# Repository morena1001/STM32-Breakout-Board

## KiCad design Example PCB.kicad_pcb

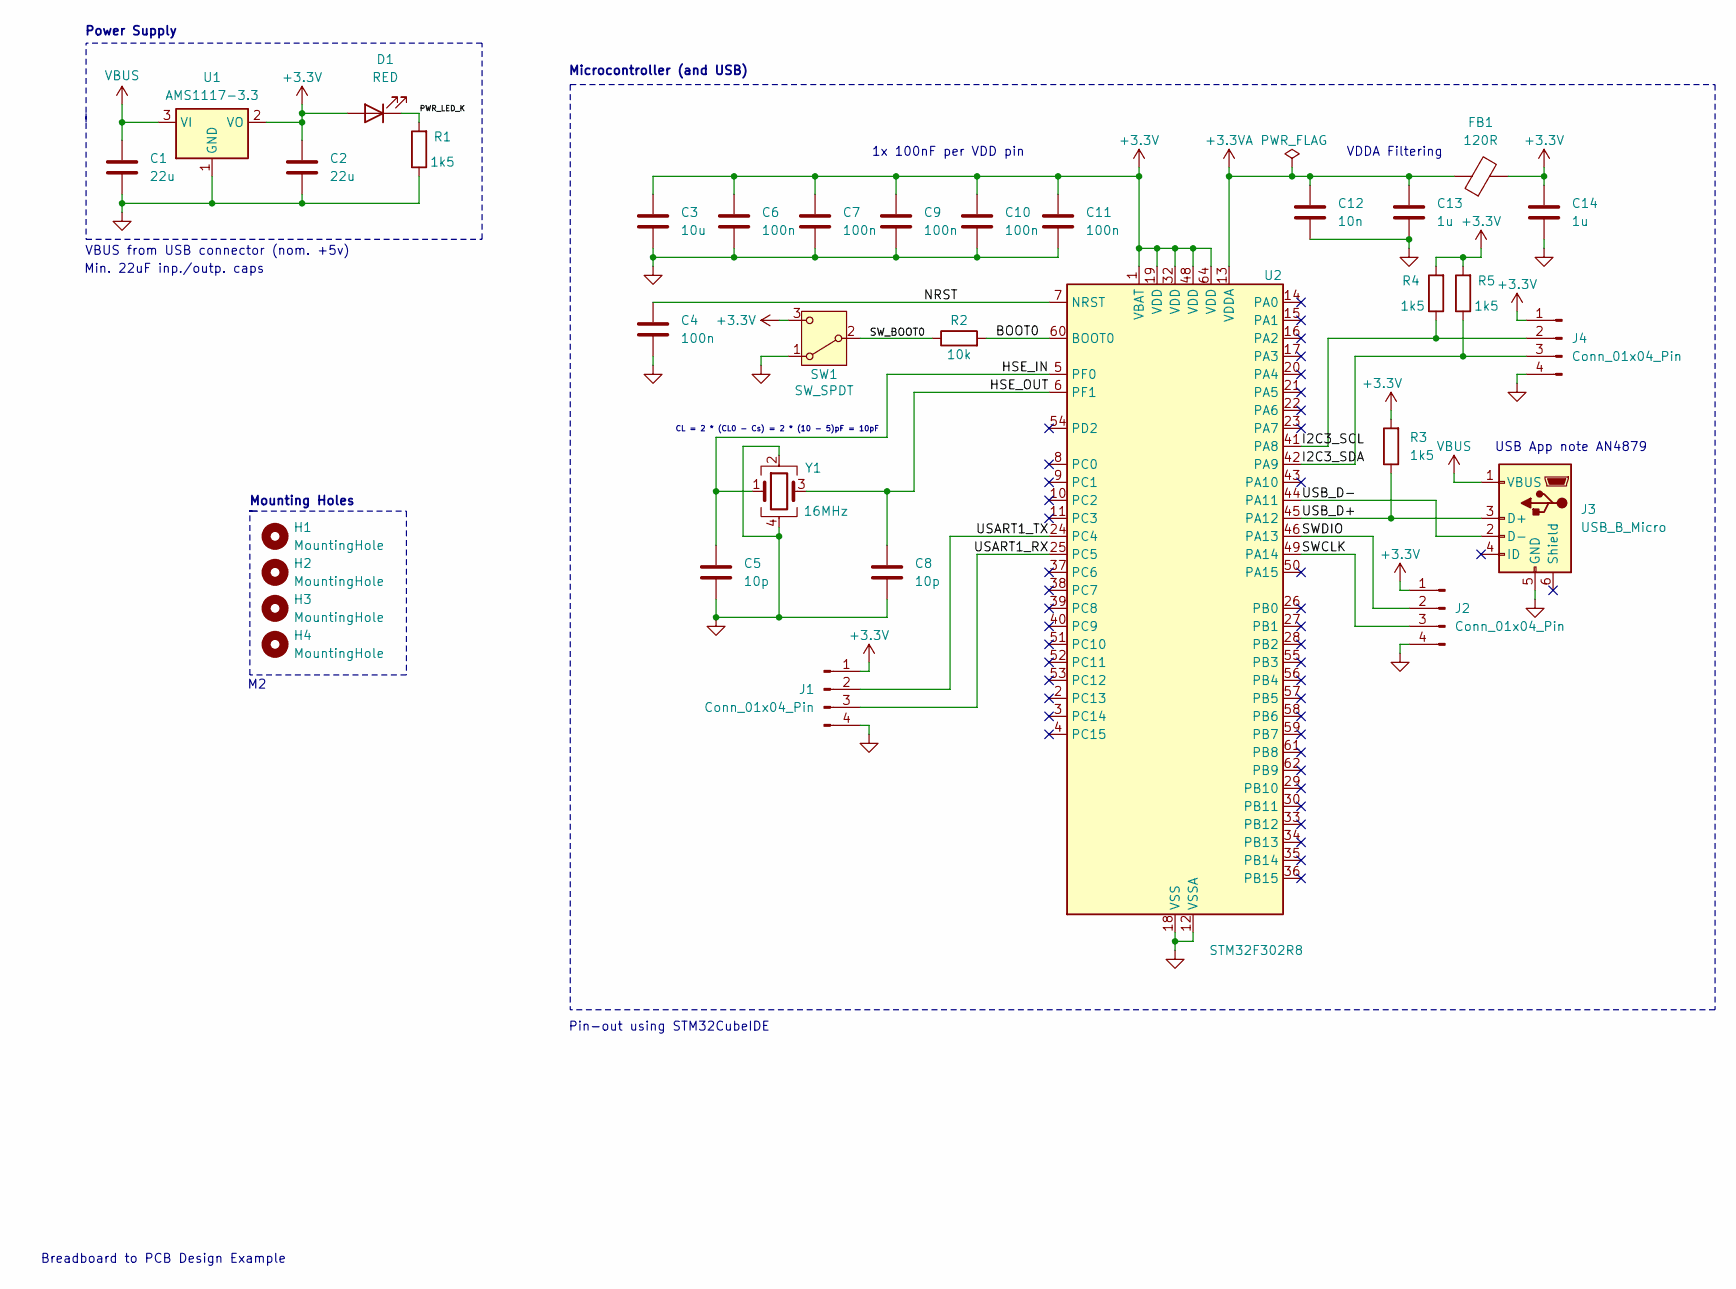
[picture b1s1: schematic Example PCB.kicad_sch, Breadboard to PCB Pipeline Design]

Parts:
C1, C2: 22u; C_0805_2012Metric
C3: 10u; C_0603_1608Metric
C4, C6, C7, C9, C10, C11: 100n; C_0402_1005Metric
C5, C8: 10p; C_0402_1005Metric
C12: 10n; C_0402_1005Metric
C13, C14: 1u; C_0402_1005Metric
D1: RED; LED_0603_1608Metric
FB1: 120R; L_0603_1608Metric
H1, H2, H3, H4: MountingHole; MountingHole_2.2mm_M2
J1, J2, J4: Conn_01x04_Pin; PinHeader_1x04_P2.54mm_Vertical
J3: USB_B_Micro; USB_Micro-B_Wuerth_629105150521
R1, R3, R4, R5: 1k5; R_0402_1005Metric
R2: 10k; R_0402_1005Metric
SW1: SW_SPDT; SW_SPDT_PCM12
U1: AMS1117-3.3; SOT-223-3_TabPin2
U2: STM32F302R8; LQFP-64_10x10mm_P0.5mm
Y1: 16MHz; Crystal_SMD_3225-4Pin_3.2x2.5mm

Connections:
+3.3V: C2.1, C3.1, C6.1, C7.1, C9.1, C10.1, C11.1, C14.1, D1.2 (A), FB1.2, J1.1, J2.1, J4.1, R3.2, R4.2, R5.2, SW1.3 (C), U1.2 (VO), U2.1 (VBAT), U2.19 (VDD), U2.32 (VDD), U2.48 (VDD), U2.64 (VDD)
+3.3VA: C12.1, C13.1, FB1.1, U2.13 (VDDA)
/BOOT0: R2.2, U2.60 (BOOT0)
/HSE_IN: C5.1, U2.5 (PF0), Y1.1
/HSE_OUT: C8.1, U2.6 (PF1), Y1.3
/I2C3_SCL: J4.2, R4.1, U2.41 (PA8)
/I2C3_SDA: J4.3, R5.1, U2.42 (PA9)
/NRST: C4.1, U2.7 (NRST)
/PWR_LED_K: D1.1 (K), R1.2
/SWCLK: J2.3, U2.49 (PA14)
/SWDIO: J2.2, U2.46 (PA13)
/SW_BOOT0: R2.1, SW1.2 (B)
/USART1_RX: J1.3, U2.25 (PC5)
/USART1_TX: J1.2, U2.24 (PC4)
/USB_D+: J3.3 (D+), R3.1, U2.45 (PA12)
/USB_D-: J3.2 (D-), U2.44 (PA11)
GND: C1.2, C2.2, C3.2, C4.2, C5.2, C6.2, C7.2, C8.2, C9.2, C10.2, C11.2, C12.2, C13.2, C14.2, J1.4, J2.4, J3.5 (GND), J4.4, R1.1, SW1.1 (A), U1.1 (GND), U2.12 (VSSA), U2.18 (VSS), U2.31 (VSS), U2.47 (VSS), U2.63 (VSS), Y1.2, Y1.4
VBUS: C1.1, J3.1 (VBUS), U1.3 (VI)

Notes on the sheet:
Pin-out using STM32CubeIDE
USB App note AN4879
Power Supply
VBUS from USB connector (nom. +5v)
Min. 22uF inp./outp. caps
Breadboard to PCB Design Example
Microcontroller (and USB)
CL = 2 * (CL0 - Cs) = 2 * (10 - 5)pF = 10pF
1x 100nF per VDD pin
Mounting Holes
VDDA Filtering

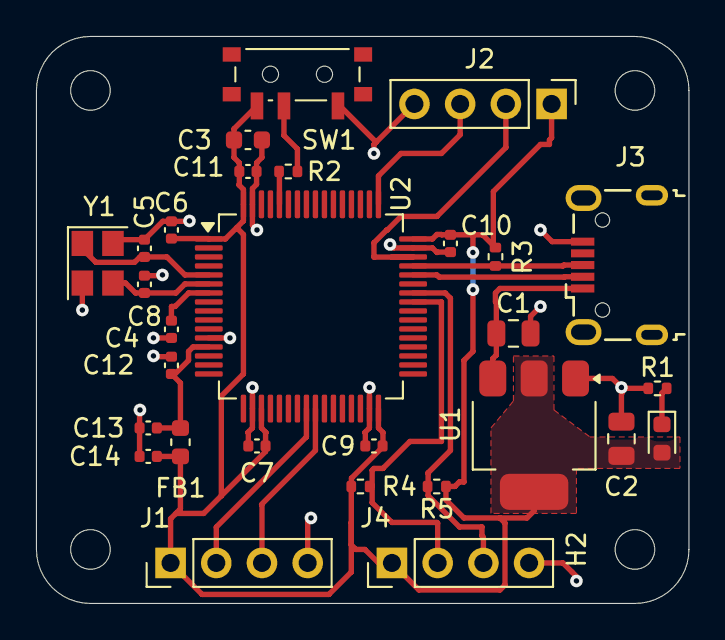
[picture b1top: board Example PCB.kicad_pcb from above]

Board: 2 copper layers, 36.2 x 31.5 mm, 33 parts (0 on the bottom side), 18 nets.

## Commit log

2024-10-14 First push
